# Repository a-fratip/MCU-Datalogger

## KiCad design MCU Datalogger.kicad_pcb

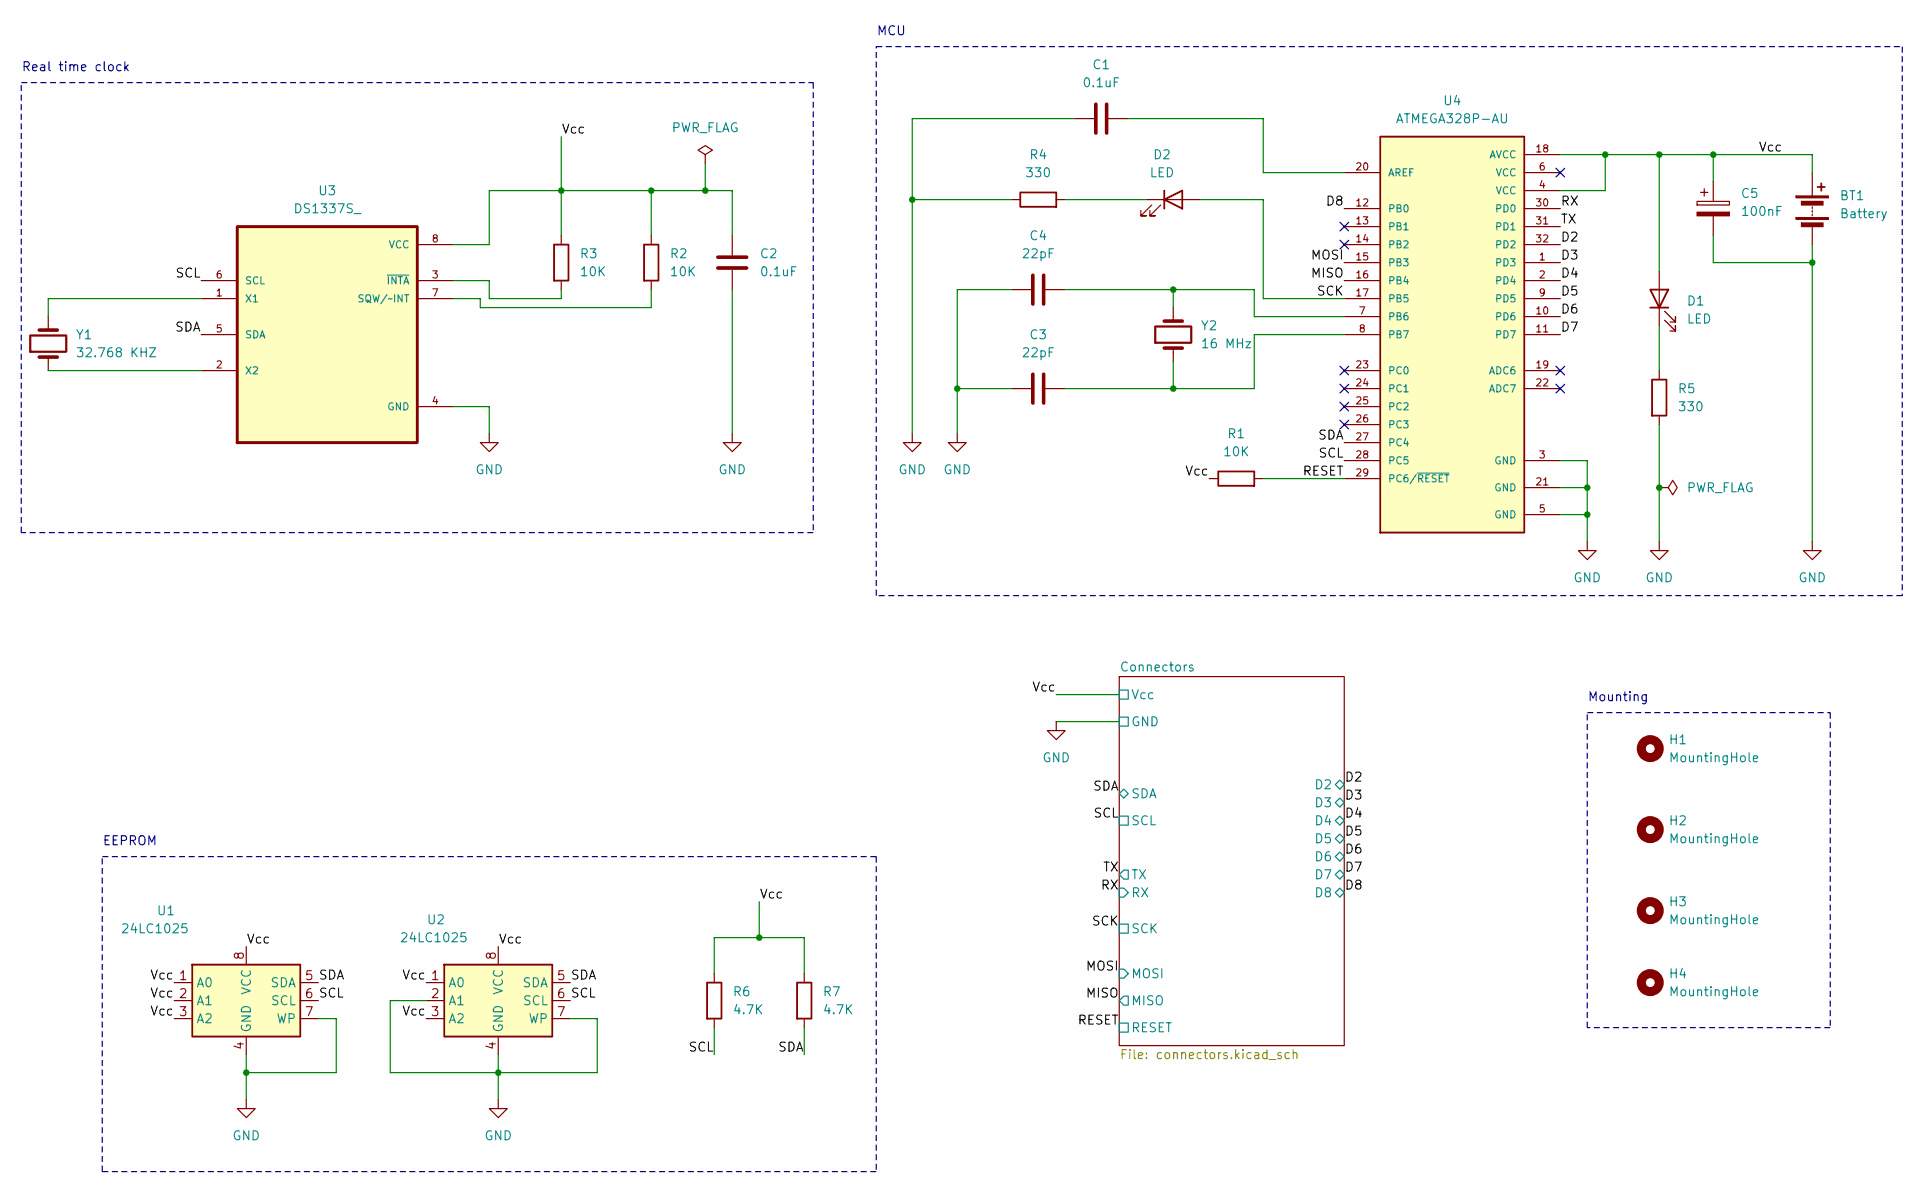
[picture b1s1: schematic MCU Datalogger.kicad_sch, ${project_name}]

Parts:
BT1: Battery; PinHeader_1x02_P2.54mm_Vertical
C1, C2: 0.1uF; C_0805_2012Metric
C3, C4: 22pF; C_0805_2012Metric
C5: 100nF; C_0805_2012Metric
D1, D2: LED; LED_0805_2012Metric
H1, H2, H3, H4: MountingHole; MountingHole_2.1mm
R1, R2, R3: 10K; R_0805_2012Metric
R4, R5: 330; R_0805_2012Metric
R6, R7: 4.7K; R_0805_2012Metric
U1, U2: 24LC1025; SOIC-8_5.23x5.23mm_P1.27mm
U3: DS1337S_; SOIC127P600X175-8N
U4: ATMEGA328P-AU; QFP80P900X900X120-32N
Y1: 32.768 KHZ; Crystal_SMD_5032-2Pin_5.0x3.2mm_HandSoldering
Y2: 16 MHz; Crystal_SMD_5032-2Pin_5.0x3.2mm_HandSoldering

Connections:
/D2: U4.32 (PD2); also elsewhere on the board
/D3: U4.1 (PD3); also elsewhere on the board
/D4: U4.2 (PD4); also elsewhere on the board
/D5: U4.9 (PD5); also elsewhere on the board
/D6: U4.10 (PD6); also elsewhere on the board
/D7: U4.11 (PD7); also elsewhere on the board
/D8: U4.12 (PB0); also elsewhere on the board
/MISO: U4.16 (PB4); also elsewhere on the board
/MOSI: U4.15 (PB3); also elsewhere on the board
/RESET: R1.2, U4.29 (PC6/~RESET); also elsewhere on the board
/RX: U4.30 (PD0); also elsewhere on the board
/SCK: D2.2 (A), U4.17 (PB5); also elsewhere on the board
/SCL: R6.2, U1.6 (SCL), U2.6 (SCL), U3.6 (SCL), U4.28 (PC5); also elsewhere on the board
/SDA: R7.2, U1.5 (SDA), U2.5 (SDA), U3.5 (SDA), U4.27 (PC4); also elsewhere on the board
/TX: U4.31 (PD1); also elsewhere on the board
/Vcc: BT1.1 (+), C2.1, C5.1, D1.2 (A), R1.1, R2.1, R3.1, R6.1, R7.1, U1.1 (A0), U1.2 (A1), U1.3 (A2), U1.8 (VCC), U2.1 (A0), U2.3 (A2), U2.8 (VCC), U3.8 (VCC), U4.4 (VCC), U4.18 (AVCC); also elsewhere on the board
GND: BT1.2 (-), C1.1, C2.2, C3.1, C4.1, C5.2, R4.1, R5.2, U1.4 (GND), U1.7 (WP), U2.2 (A1), U2.4 (GND), U2.7 (WP), U3.4 (GND), U4.3 (GND), U4.5 (GND), U4.21 (GND); also elsewhere on the board
unnamed: D1.1 (K), R5.1
unnamed: D2.1 (K), R4.2
unnamed: R2.2, U3.7 (SQW/~INT)
unnamed: U3.1 (X1), Y1.2
unnamed: U3.2 (X2), Y1.1
unnamed: R3.2, U3.3 (~INTA)
unnamed: C1.2, U4.20 (AREF)
unnamed: C4.2, U4.7 (PB6), Y2.2
unnamed: C3.2, U4.8 (PB7), Y2.1

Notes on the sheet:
EEPROM
MCU
Mounting
Real time clock

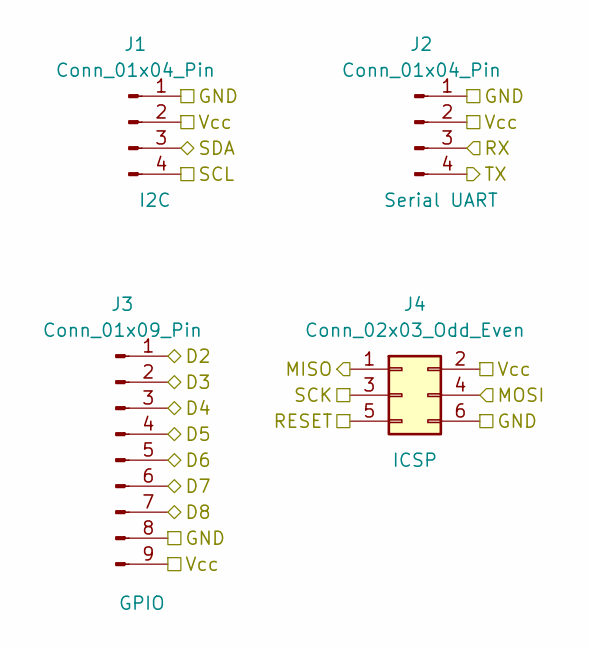
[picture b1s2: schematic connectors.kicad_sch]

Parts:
J1, J2: Conn_01x04_Pin; PinHeader_1x04_P2.54mm_Vertical
J3: Conn_01x09_Pin; PinHeader_1x09_P2.54mm_Vertical
J4: Conn_02x03_Odd_Even; PinHeader_2x03_P2.54mm_Vertical

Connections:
/D2: J3.1; also elsewhere on the board
/D3: J3.2; also elsewhere on the board
/D4: J3.3; also elsewhere on the board
/D5: J3.4; also elsewhere on the board
/D6: J3.5; also elsewhere on the board
/D7: J3.6; also elsewhere on the board
/D8: J3.7; also elsewhere on the board
/MISO: J4.1; also elsewhere on the board
/MOSI: J4.4; also elsewhere on the board
/RESET: J4.5; also elsewhere on the board
/RX: J2.3; also elsewhere on the board
/SCK: J4.3; also elsewhere on the board
/SCL: J1.4; also elsewhere on the board
/SDA: J1.3; also elsewhere on the board
/TX: J2.4; also elsewhere on the board
/Vcc: J1.2, J2.2, J3.9, J4.2; also elsewhere on the board
GND: J1.1, J2.1, J3.8, J4.6; also elsewhere on the board

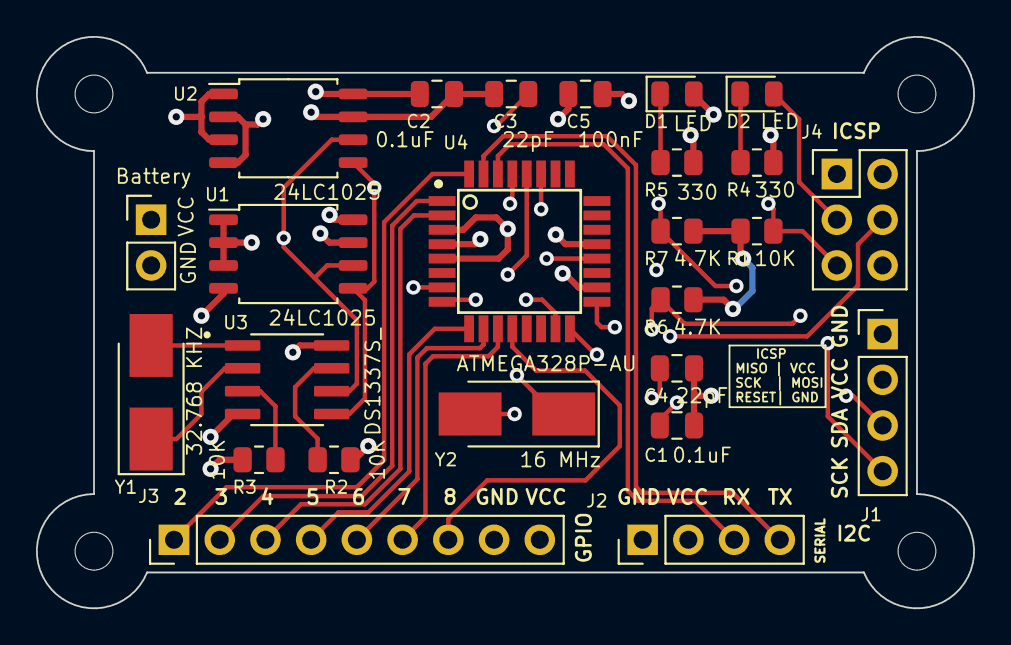
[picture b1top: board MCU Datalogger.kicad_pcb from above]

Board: 4 copper layers, 52.1 x 31.7 mm, 29 parts (0 on the bottom side), 26 nets.

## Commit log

2024-07-07 First commit of new project.
2024-07-07 Setup of EEschema for new project.
2024-07-08 Have added required symbols to the schematic sheets.
2024-07-09 Changed locations of symbols (arrange).
2024-07-09 Added component values.
2024-07-27 Completed symbol-footprint associations.
2024-07-28 Completed wiring of main sheet.
2024-07-29 Completed wiring in second sheet.
2024-07-29 Allocated GND and Vcc nets to the Power net class.
2024-07-29 Completed comments.
2024-08-03 Setup Pcbnew.
2024-08-03 Added untracked file.
2024-08-03 Completed placement of footprints.
2024-08-06 Routing without GND VCC completed.
2024-08-17 Completed routing.
2024-08-17 Refined routing complete.
2024-08-19 Fixed outstanding issues.
2024-08-19 Completed final DRC.
2024-08-19 Completed 2-layer PCB.
2024-08-20 Completed 4-layer pcb routing.
2024-08-24 Added gitattributes file to prevent PCB files from merge.
2024-08-24 Fixed two defects in the schematic.
2024-08-25 Fixed net bugs in 4 layer version of the PCB.
